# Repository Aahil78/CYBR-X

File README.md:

# CYBR-X -- A Custom, 16 Key Macropad

CYBR-X is a custom macropad that has:
- 16 Hotswappable, MX Style Keys
- Per-key SK6812 RGB Baclight
- Based off of the Seeed Studio XIAO RP2040
- 2 Rotary Encoders
- 0.91" OLED Display
- Customizable Firmware
- A custom 3D-Printed Case
- And more!

------ 

# Images

## PCB

## Schematic

## Full Assembly

The switches go into the plate, the plate and bottom sandwich the PCB then, and thats how assembly is done.

# Bill Of Materials
Here's the BOM for my macropad:
| Name                               | Quantity |
|----------------------------------- |----------|
| Seeed Studio XIAO RP2040           | 1        |
| MCP23017 I2C I/O Expander          | 1        |
| BSS138 MOSFET                      | 1        |
| 1N4148 Diode (Through-hole)        | 16       |
| MX-Style Switch                    | 16       |
| Kailh MX-Style Hotswap Socket      | 16       |
| Blank DSA Keycap (White)           | 16       |
| EC11 With Switch                   | 2        |
| SK6812 MINI-E RGB LED              | 16       |
| 0.1uF 0805 Ceramic Capacitor       | 16       |
| 10kΩ 0805 Resistor                 | 4        |
| 0.91" OLED I2C Display             | 1        |
| M3x16mm Screw                      | -        |
| M3x5mx4mm Heatset Insert           | -        |
| 3D Printed Case (2 Parts)          | 1        |
| Main PCB                           | MOQ: 5   |

For the screws and inserts, as many as there are in kit is fine but minimum is 4.

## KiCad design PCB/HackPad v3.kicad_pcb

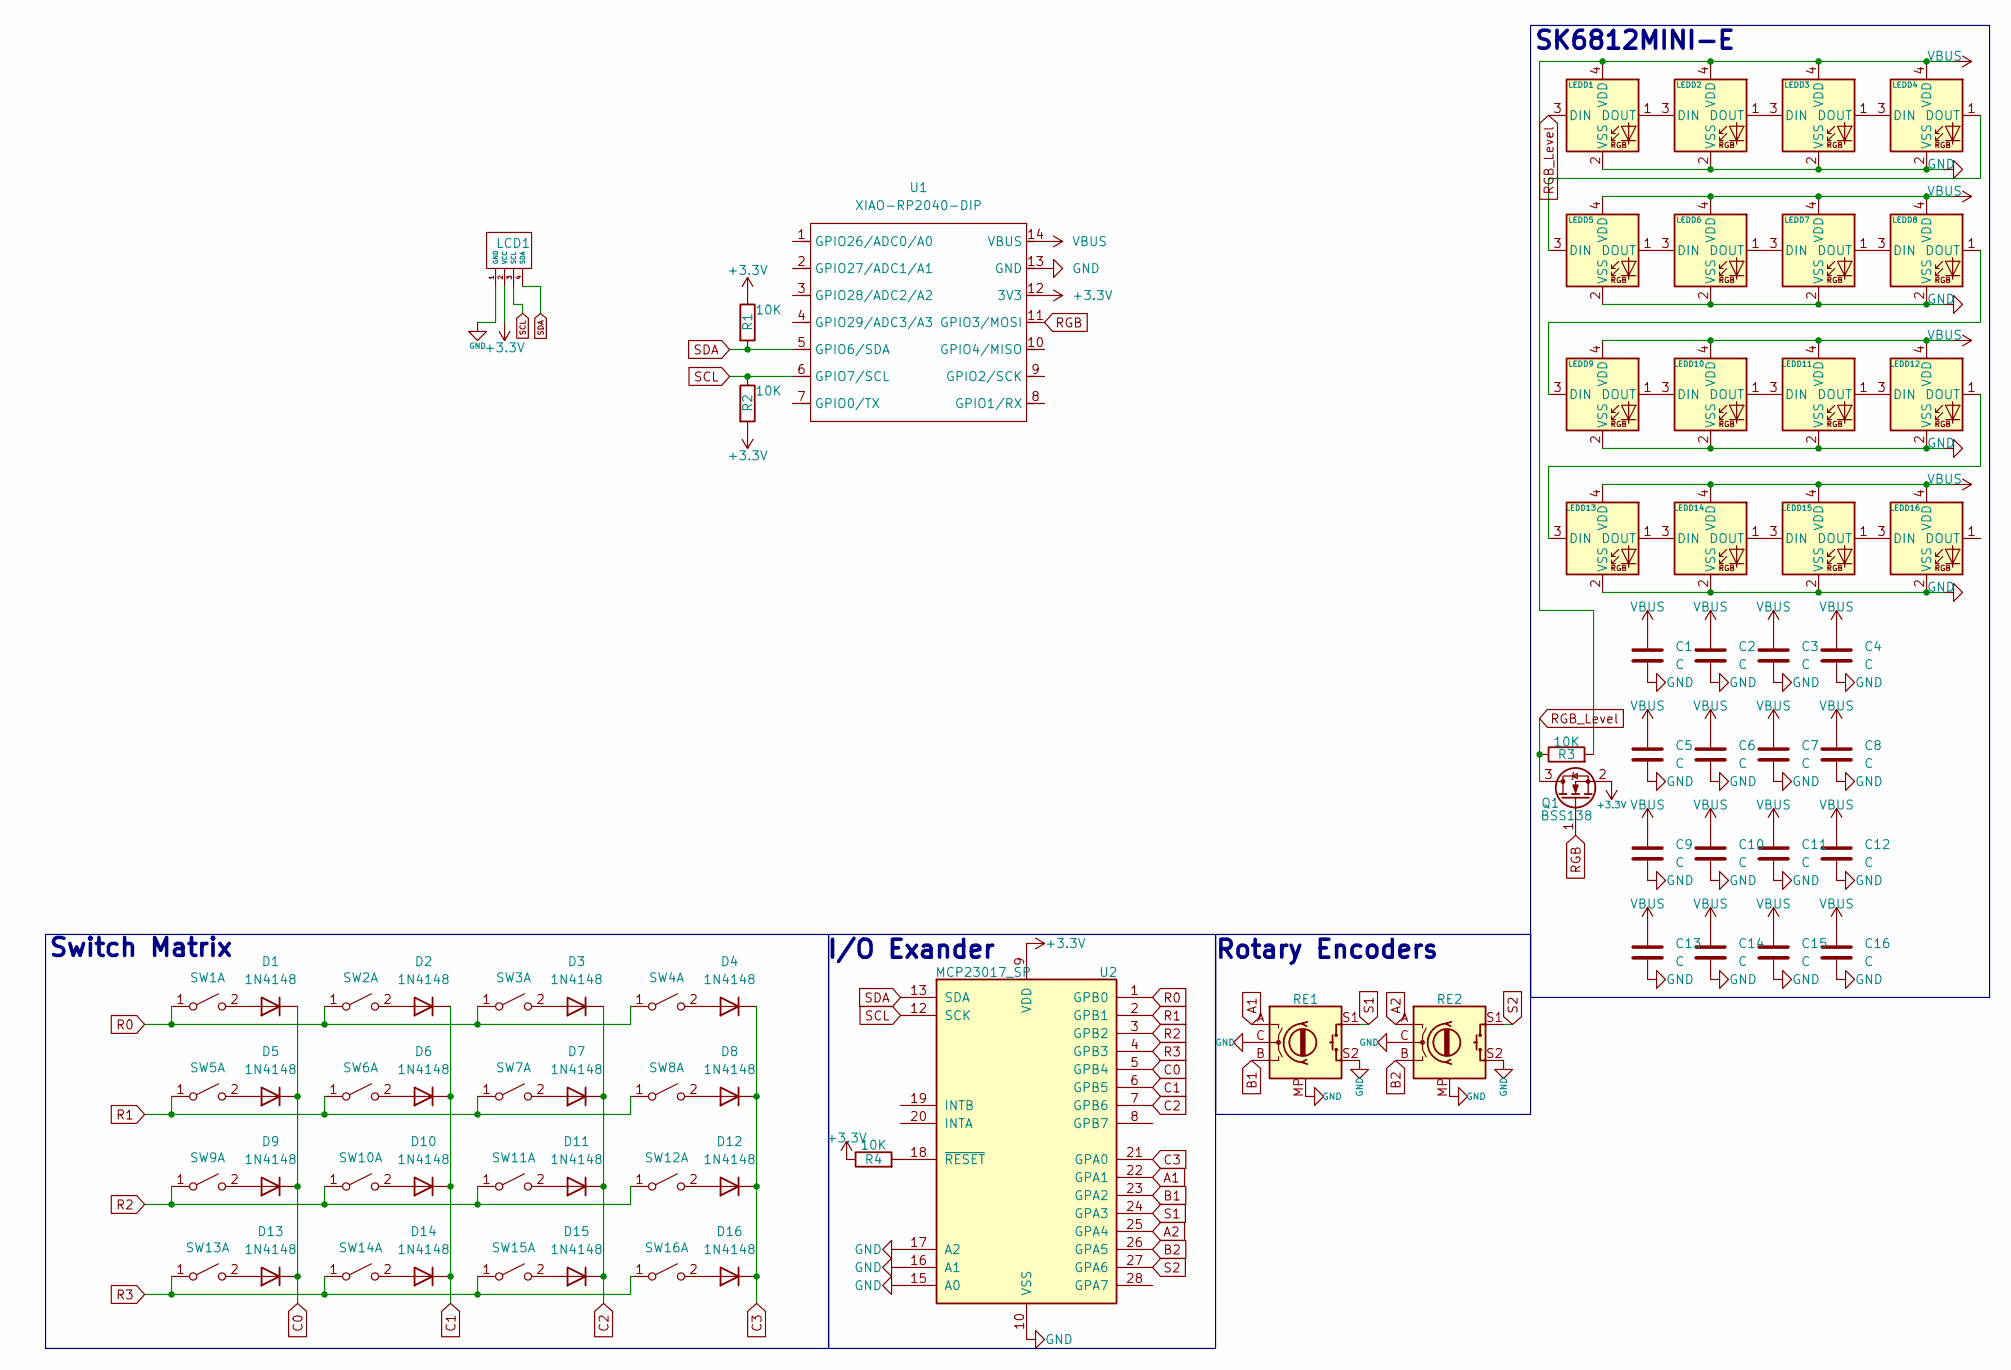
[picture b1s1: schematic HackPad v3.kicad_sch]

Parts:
C1, C2, C3, C4, C5, C6, C7, C8, C9, C10, C11, C12, C13, C14, C15, C16: C; C_0805_2012Metric
D1, D2, D3, D4, D5, D6, D7, D8, D9, D10, D11, D12, D13, D14, D15, D16: 1N4148; D_DO-35_SOD27_P7.62mm_Horizontal
LCD1: SSD1306-0.91-OLED-4pin-128x32
LEDD1, LEDD2, LEDD3, LEDD4, LEDD5, LEDD6, LEDD7, LEDD8, LEDD9, LEDD10, LEDD11, LEDD12, LEDD13, LEDD14, LEDD15, LEDD16: SK6812MINI; MX_SK6812MINI-E
Q1: BSS138; SOT-23
R1, R2, R3, R4: 10K; R_0805_2012Metric
RE1, RE2: RotaryEncoder_Switch_MP; RotaryEncoder_Alps_EC11E-Switch_Vertical_H20mm
SW1, SW2, SW3, SW4, SW5, SW6, SW7, SW8, SW9, SW10, SW11, SW12, SW13, SW14, SW15, SW16: SW_MEC_5G; SW_Hotswap_Kailh_MX_1.00u
U1: XIAO-RP2040-DIP; MOUDLE14P-XIAO-DIP-SMD
U2: MCP23017_SP; SSOP-28_5.3x10.2mm_P0.65mm

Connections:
+3.3V: LCD1.2 (VCC), Q1.2 (S), R1.1, R2.2, R4.1, U1.12 (3V3), U2.9 (VDD)
A1: RE1.A, U2.22 (GPA1)
A2: RE2.A, U2.25 (GPA4)
B1: RE1.B, U2.23 (GPA2)
B2: RE2.B, U2.26 (GPA5)
C0: D1.1 (K), D5.1 (K), D9.1 (K), D13.1 (K), U2.5 (GPB4)
C1: D2.1 (K), D6.1 (K), D10.1 (K), D14.1 (K), U2.6 (GPB5)
C2: D3.1 (K), D7.1 (K), D11.1 (K), D15.1 (K), U2.7 (GPB6)
C3: D4.1 (K), D8.1 (K), D12.1 (K), D16.1 (K), U2.21 (GPA0)
GND: C1.2, C2.2, C3.2, C4.2, C5.2, C6.2, C7.2, C8.2, C9.2, C10.2, C11.2, C12.2, C13.2, C14.2, C15.2, C16.2, LCD1.1 (GND), LEDD1.2 (VSS), LEDD2.2 (VSS), LEDD3.2 (VSS), LEDD4.2 (VSS), LEDD5.2 (VSS), LEDD6.2 (VSS), LEDD7.2 (VSS), LEDD8.2 (VSS), LEDD9.2 (VSS), LEDD10.2 (VSS), LEDD11.2 (VSS), LEDD12.2 (VSS), LEDD13.2 (VSS), LEDD14.2 (VSS), LEDD15.2 (VSS), LEDD16.2 (VSS), RE1.C, RE1.MP, RE1.S2, RE2.C, RE2.MP, RE2.S2, U1.13 (GND), U2.10 (VSS), U2.15 (A0), U2.16 (A1), U2.17 (A2)
unnamed: D1.2 (A), SW1.2 (B)
unnamed: D2.2 (A), SW2.2 (B)
unnamed: D3.2 (A), SW3.2 (B)
unnamed: D4.2 (A), SW4.2 (B)
unnamed: D5.2 (A), SW5.2 (B)
unnamed: D6.2 (A), SW6.2 (B)
unnamed: D7.2 (A), SW7.2 (B)
unnamed: D8.2 (A), SW8.2 (B)
unnamed: D9.2 (A), SW9.2 (B)
unnamed: D10.2 (A), SW10.2 (B)
unnamed: D11.2 (A), SW11.2 (B)
unnamed: D12.2 (A), SW12.2 (B)
unnamed: D13.2 (A), SW13.2 (B)
unnamed: D14.2 (A), SW14.2 (B)
unnamed: D15.2 (A), SW15.2 (B)
unnamed: D16.2 (A), SW16.2 (B)
unnamed: LEDD1.1 (DOUT), LEDD2.3 (DIN)
unnamed: LEDD2.1 (DOUT), LEDD3.3 (DIN)
unnamed: LEDD3.1 (DOUT), LEDD4.3 (DIN)
unnamed: LEDD4.1 (DOUT), LEDD5.3 (DIN)
unnamed: LEDD5.1 (DOUT), LEDD6.3 (DIN)
unnamed: LEDD6.1 (DOUT), LEDD7.3 (DIN)
unnamed: LEDD7.1 (DOUT), LEDD8.3 (DIN)
unnamed: LEDD8.1 (DOUT), LEDD9.3 (DIN)
unnamed: LEDD9.1 (DOUT), LEDD10.3 (DIN)
unnamed: LEDD10.1 (DOUT), LEDD11.3 (DIN)
unnamed: LEDD11.1 (DOUT), LEDD12.3 (DIN)
unnamed: LEDD12.1 (DOUT), LEDD13.3 (DIN)
unnamed: LEDD13.1 (DOUT), LEDD14.3 (DIN)
unnamed: LEDD14.1 (DOUT), LEDD15.3 (DIN)
unnamed: LEDD15.1 (DOUT), LEDD16.3 (DIN)
unnamed: R4.2, U2.18 (~RESET)
R0: SW1.1 (A), SW2.1 (A), SW3.1 (A), SW4.1 (A), U2.1 (GPB0)
R1: SW5.1 (A), SW6.1 (A), SW7.1 (A), SW8.1 (A), U2.2 (GPB1)
R2: SW9.1 (A), SW10.1 (A), SW11.1 (A), SW12.1 (A), U2.3 (GPB2)
R3: SW13.1 (A), SW14.1 (A), SW15.1 (A), SW16.1 (A), U2.4 (GPB3)
RGB: Q1.1 (G), U1.11 (GPIO3/MOSI)
RGB_Level: LEDD1.3 (DIN), Q1.3 (D), R3.1
S1: RE1.S1, U2.24 (GPA3)
S2: RE2.S1, U2.27 (GPA6)
SCL: LCD1.3 (SCL), R2.1, U1.6 (GPIO7/SCL), U2.12 (SCK)
SDA: LCD1.4 (SDA), R1.2, U1.5 (GPIO6/SDA), U2.13 (SDA)
VBUS: C1.1, C2.1, C3.1, C4.1, C5.1, C6.1, C7.1, C8.1, C9.1, C10.1, C11.1, C12.1, C13.1, C14.1, C15.1, C16.1, LEDD1.4 (VDD), LEDD2.4 (VDD), LEDD3.4 (VDD), LEDD4.4 (VDD), LEDD5.4 (VDD), LEDD6.4 (VDD), LEDD7.4 (VDD), LEDD8.4 (VDD), LEDD9.4 (VDD), LEDD10.4 (VDD), LEDD11.4 (VDD), LEDD12.4 (VDD), LEDD13.4 (VDD), LEDD14.4 (VDD), LEDD15.4 (VDD), LEDD16.4 (VDD), R3.2, U1.14 (VBUS)

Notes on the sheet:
Rotary Encoders
I/O Exander
SK6812MINI-E
Switch Matrix

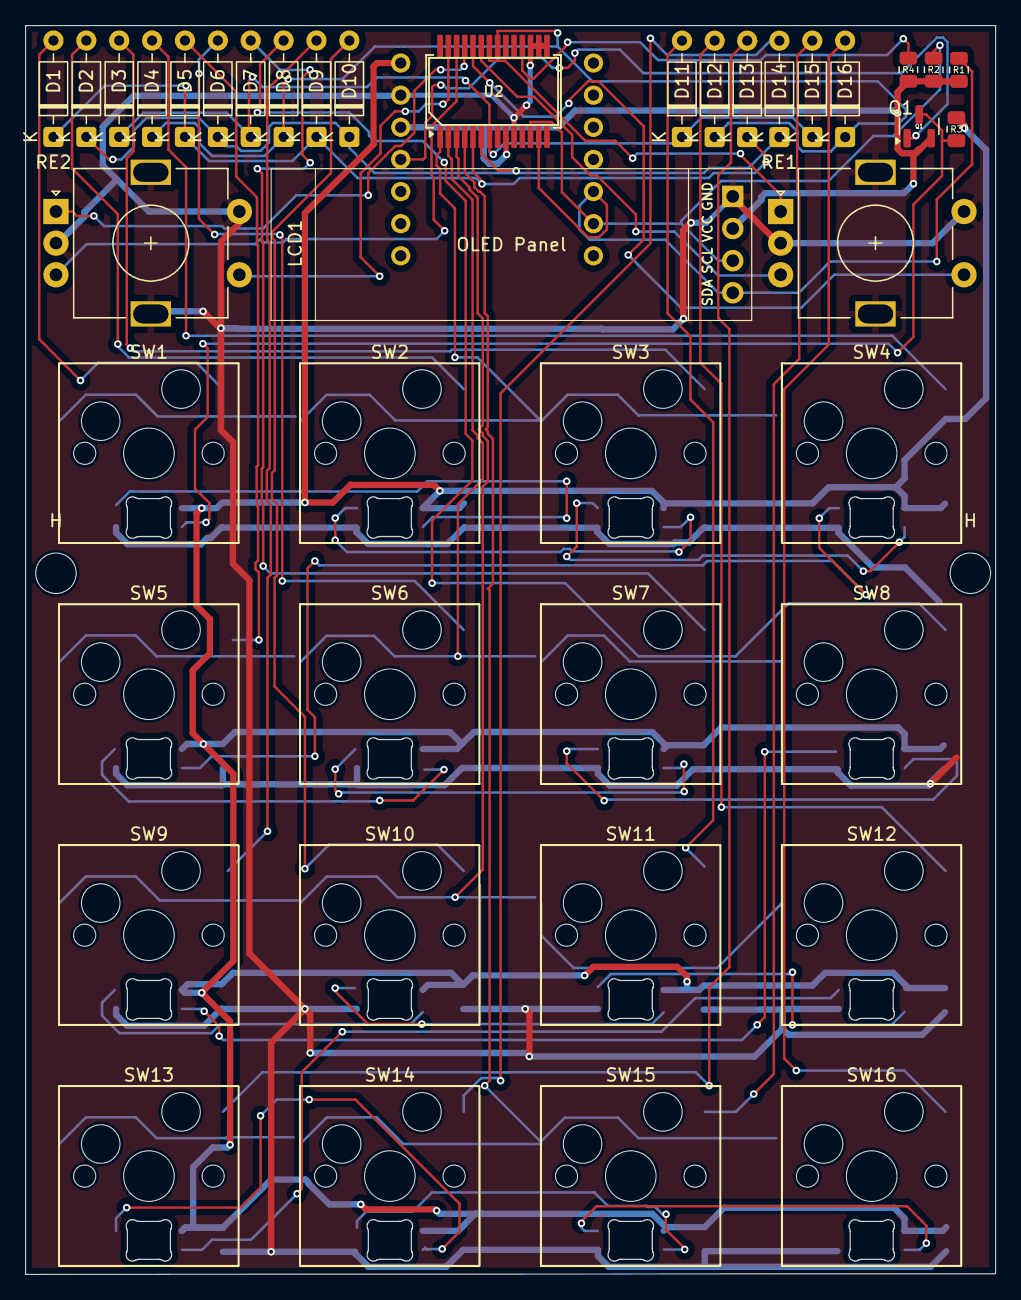
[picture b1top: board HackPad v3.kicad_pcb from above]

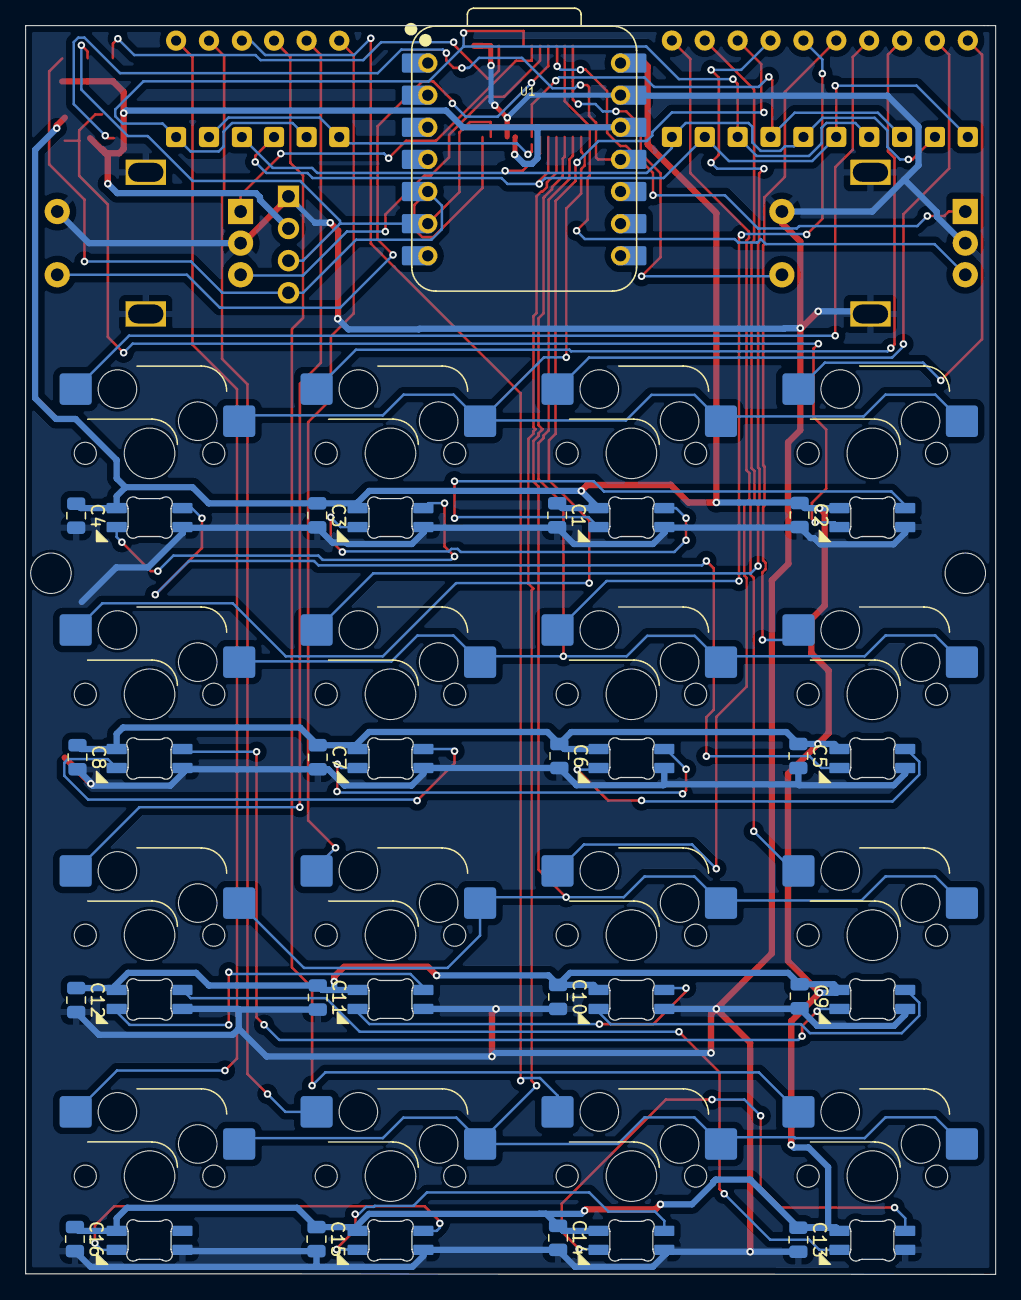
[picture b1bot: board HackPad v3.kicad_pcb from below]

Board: 2 copper layers, 76.7 x 98.7 mm, 76 parts (17 on the bottom side), 53 nets.

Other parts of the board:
H: MountingHole_3.2mm_M3
H#2: MountingHole_3.2mm_M3

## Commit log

2025-06-11 Add all necessary files
2025-06-11 Add images and fix a typo in readme
2025-06-11 Update PCB and Gerber
2025-06-12 Update files
2025-06-14 Change PCB and Gerber
